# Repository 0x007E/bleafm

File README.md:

# bleafm
Bluetooth FM Audio Transmitter

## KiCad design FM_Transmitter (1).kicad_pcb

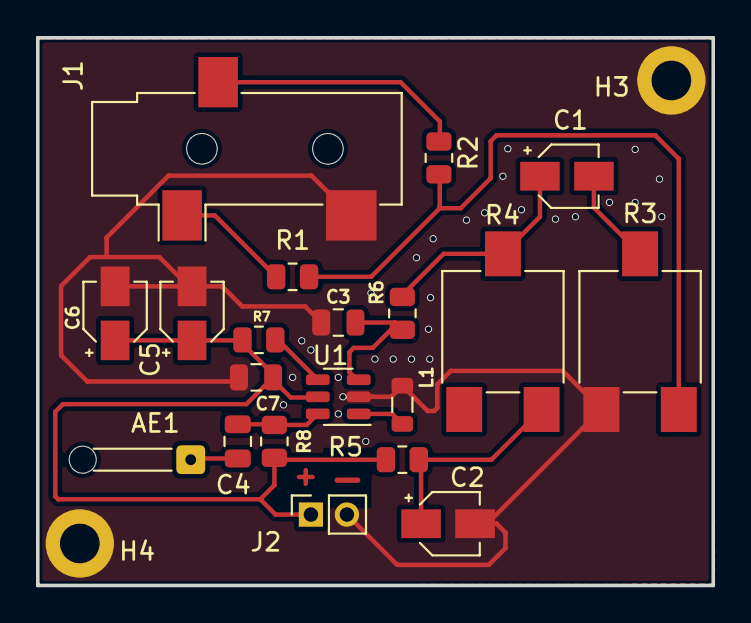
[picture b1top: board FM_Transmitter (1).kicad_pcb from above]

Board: 2 copper layers, 37.5 x 30.4 mm, 22 parts (0 on the bottom side), 13 nets.

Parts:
AE1: Antenna; SolderWire-0.1sqmm_1x01_D0.4mm_OD1mm_Relief
C1: 0.47µ; CP_Elec_3x5.3
C2: 10µ; CP_Elec_3x5.3
C3: 2200p; C_0805_2012Metric
C4: 1000p; C_0805_2012Metric
C5: 10n; CP_Elec_3x5.3
C6: 1µ; CP_Elec_3x5.3
C7: 100; C_0805_2012Metric
H3, H4: MountingHole_Pad; MountingHole_2.2mm_M2_DIN965_Pad
J1: AudioJack3; Jack_3.5mm_CUI_SJ-3523-SMT_Horizontal
J2: Conn_01x02_Female; PinSocket_1x02_P2.00mm_Vertical
L1: 390nH; L_0805_2012Metric
R1, R2: 22k; R_0805_2012Metric
R3: 10k; Potentiometer_ACP_CA6-VSMD_Vertical
R4: 100k; Potentiometer_ACP_CA6-VSMD_Vertical
R5: 4.7k; R_0805_2012Metric
R6: 270; R_0805_2012Metric
R7, R8: 1k; R_0805_2012Metric
U1: MAX2606; SOT-23-6

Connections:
+5V: C5.1, C6.1, C7.1, J2.1, R5.1, R7.1, R8.2, U1.5 (VCC)
GND: C2.2, C3.2, C5.2, C6.2, C7.2, H3.1, H4.1, J1.T, J2.2, L1.2, R3.3, U1.2 (GND)
unnamed: AE1.1 (A), C4.2
unnamed: C1.1, R4.2, R6.2
unnamed: C1.2, R3.2
unnamed: C2.1, R4.1, R5.2
unnamed: C3.1, R6.1, U1.3 (TUNE)
unnamed: C4.1, R8.1, U1.6 (OUT+)
unnamed: J1.R, R2.2
unnamed: J1.S, R1.1
unnamed: L1.1, U1.1 (IND)
unnamed: R1.2, R2.1, R3.1
unnamed: R7.2, U1.4 (OUT-)

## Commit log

2022-12-07 Schaltplan
2022-12-14 kontrolle Board bitte
2022-12-16 Board Emircan bittäääää
2022-12-16 kicud emircan
2022-12-23 Bohrplan und Gerbedateien
